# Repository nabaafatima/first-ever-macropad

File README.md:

# Fusionpad
### A macropad with 4 keys i made for hackclub mqacondo program. I used KiCad and fusion360 for the first time!
# Features
- 4 reprogramable keys
# My Complete 3D model

# CAD
### I created the the case for my macropad using Fusion 360. Since it was my firts time using it. I couldnt understand how to make screw holes so i used the fitting method. It took a long time. The case consists of 2 parts. The lid an the bottom part

# PCB
### Used KiCad for it. And it was also my first time

# Firmware
### I used KMK and it was my first time using it. thats why i had to do a lot of research for it to go well. Searched for all the possible shortcuts and found these the most helpful:
- key 1 -> copy
- key2 -> paste
- key 3 -> undo
- key 4 -> rdeo
  
# BOM
|product|price|link|
|:---:|:---:|:---:|
|MX switch|9.60|[buy](https://www.aliexpress.com/item/4000100166477.html?spm=a2g0n.productlist.0.0.5d422464LBuJkQ&browser_id=88688e762c4b4ac592af2021b8ba8817&aff_platform=msite&m_page_id=rjdwismp7vocaxrh19fe0c04227247d6e50a35c1b8&gclid=&pdp_ext_f=%7B%22order%22%3A%2229%22%2C%22eval%22%3A%221%22%2C%22fromPage%22%3A%22search%22%7D&pdp_npi=6%40dis%21PKR%212883.33%212708.77%21%21%219.25%218.69%21%40ac10c6f117861821240587633d4451%2110000000263150986%21sea%21PK%210%21ABX%211%210%21n_tag%3A-29910%3Bd%3A88b7f846%3Bm03_new_user%3A-29895&algo_pvid=fc0baad9-8cc8-423f-a047-dd8736d333ec&utparam-url=scene%3Asearch%7Cquery_from%3A%7Cx_object_id%3A4000100166477%7C_p_origin_prod%3A)
|seeed studio esp32|10.99|[buy](https://www.aliexpress.com/item/1005006951950465.html?spm=a2g0n.productlist.0.0.4a814c20TfvDCc&browser_id=88688e762c4b4ac592af2021b8ba8817&aff_platform=msite&m_page_id=rjdwismp7vocaxrh19fe0c314ff1d62b447f27f14a&gclid=&pdp_ext_f=%7B%22order%22%3A%22273%22%2C%22eval%22%3A%221%22%2C%22fromPage%22%3A%22search%22%7D&pdp_npi=6%40dis%21PKR%2115118.00%2110884.96%21%21%2148.50%2134.92%21%40ac10c0bf17861823091075510dbae2%2112000047076999704%21sea%21PK%210%21ABX%211%210%21n_tag%3A-29910%3Bd%3A88b7f846%3Bm03_new_user%3A-29895&isseo=y&algo_pvid=e931d695-296a-42d6-9d0b-ae3af8d65b24&utparam-url=scene%3Asearch%7Cquery_from%3A%7Cx_object_id%3A1005006951950465%7C_p_origin_prod%3A)
|Keycaps|2.58 for 10|[buy](https://www.aliexpress.com/item/1005008827240220.html?spm=a2g0n.productlist.0.0.2d787b89Wych7K&browser_id=88688e762c4b4ac592af2021b8ba8817&aff_platform=msite&m_page_id=rjdwismp7vocaxrh1a1062c3e3e198b9f1cb1688d0&gclid=&pdp_ext_f=%7B%22order%22%3A%221489%22%2C%22spu_best_type%22%3A%22price%22%2C%22eval%22%3A%221%22%2C%22fromPage%22%3A%22search%22%7D&pdp_npi=6%40dis%21PKR%21714.81%21711.66%21%21%212.27%212.26%21%402102eb1417911049252034253e0f35%2112000046843776636%21sea%21PK%210%21ABX%211%210%21n_tag%3A-29910%3Bd%3A88b7f846%3Bm03_new_user%3A-29895%3BpisId%3A5000000216890786&isseo=y&algo_pvid=ed0f8664-520b-4492-aec7-cdbeb7161844&utparam-url=scene%3Asearch%7Cquery_from%3A%7Cx_object_id%3A1005008827240220%7C_p_origin_prod%3A)
|Case| - |[link](https://github.com/nabaafatima/first-ever-macropad/blob/main/CAD/bottom%2Bpart.stl)
|plate| - |[link](https://github.com/nabaafatima/first-ever-macropad/blob/main/CAD/plate.stl)
| pcb |16.22|[link](https://cart.jlcpcb.com/shopcart/cart/)
# Information
## Inspiration
#### i have done a lots of software projects and wanted to try hardware too. Thus after some research decided to go for a macropad. I found many resources online so it helped me a lot.
## Challenges 
#### Designing the case was the most difficult also i used fusion for the firts time. KiCad was dfficult ot use too but the controls in KiCadwere normal. Fusion had evrything jumbled up.

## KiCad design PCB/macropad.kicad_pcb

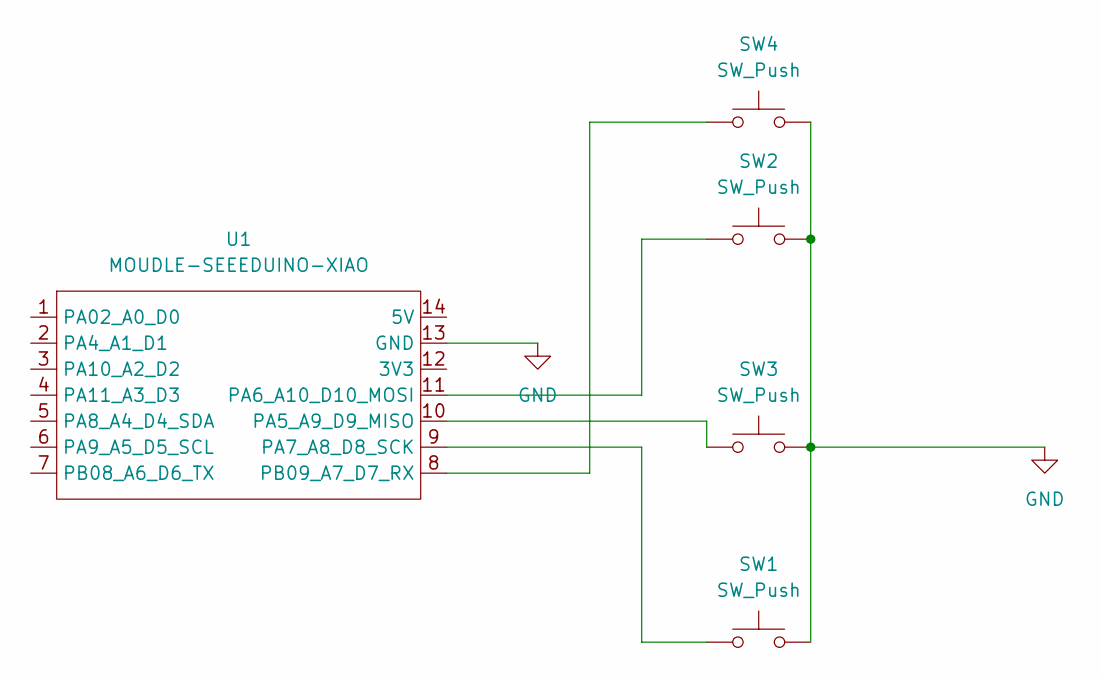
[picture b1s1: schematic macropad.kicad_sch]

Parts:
SW1, SW2, SW3, SW4: SW_Push; SW_Cherry_MX_1.00u_PCB
U1: MOUDLE-SEEEDUINO-XIAO; XIAO-Generic-Hybrid-14P-2.54-21X17.8MM

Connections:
GND: SW1.2, SW2.2, SW3.2, SW4.2, U1.13 (GND)
unnamed: SW3.1, U1.10 (PA5_A9_D9_MISO)
unnamed: SW2.1, U1.11 (PA6_A10_D10_MOSI)
unnamed: SW1.1, U1.9 (PA7_A8_D8_SCK)
unnamed: SW4.1, U1.8 (PB09_A7_D7_RX)

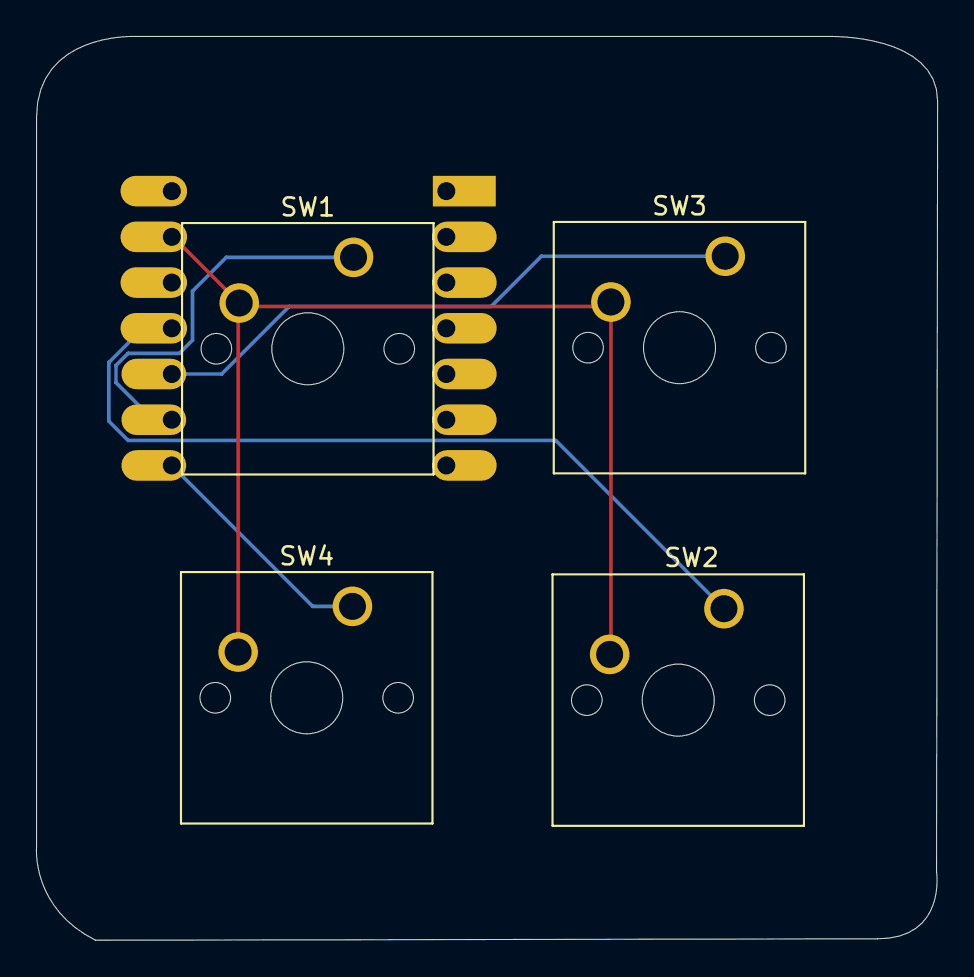
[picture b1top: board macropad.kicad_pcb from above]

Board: 2 copper layers, 50.1 x 50.2 mm, 5 parts (1 on the bottom side), 5 nets.

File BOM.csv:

"Reference","Qty","Value","Footprint", "Comment","unit price","link"
"SW1,SW2,SW3,SW4","4","SW_Push","Button_Switch_Keyboard:SW_Cherry_MX_1.00u_PCB", " Cherry Mx switch","9.60 for 16 pack"," https://www.aliexpress.com/item/1005006951950465.html?spm=a2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"
"U1","1","MOUDLE-SEEEDUINO-XIAO","footprints:XIAO-Generic-Hybrid-14P-2.54-21X17.8MM", " Seed studio samd21", "10.99","https://www.aliexpress.com/item/4000100166477.html?spm=a2g0n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"
